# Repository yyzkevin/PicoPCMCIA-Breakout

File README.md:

## Connectors

The PicoPCMCIA External I/O uses Hirose ST-series connectors, chosen for their compact size and robust locking mechanism.

🔗 **Hirose ST Series:**  
https://www.hirose.com/en/product/series/ST

### Connector Part Numbers

| Description | Part Number |
|------------|-------------|
| **Card Receptacle** | ST60-18P(30) |
| **Breakout Plug** | ST60X-18S(30) |
| **Cable Plug Assembly** | ST40X-18S-CV(30) |
| **Cable Bushing** | ST40X-BS(4.0) |
| **Cable Clamp (4 mm)** | ST40X-CM |

## Pinout
| Pin | Signal       | Notes                                                   |
| --: | ------------ | ------------------------------------------------------- |
|   1 | **SWCLK**    | RP2354 Serial Wire Debug (SWD)                          |
|   2 | **SWDIO**    | RP2354 Serial Wire Debug (SWD)                          |
|   3 | **GPIO34**   | User I/O: GPIO, UART0 TX, or I²C1 SDA                   |
|   4 | **GPIO35**   | User I/O: GPIO, UART0 RX, or I²C1 SCL                   |
|   5 | **USB D−**   | RP2354 USB Port                                         |
|   6 | **USB D+**   | RP2354 USB Port                                         |
|   7 | **BOOTSEL**  | Boot select (firmware flashing / recovery)              |
|   8 | **5V**       | 5 V from PC bus (350 mA fused)                          |
|   9 | **GND**      | Ground                                                  |
|  10 | **I2C0 SDA** | I²C master (onboard DSP + external peripherals)         |
|  11 | **I2C0 SCL** | I²C master (onboard DSP + external peripherals)         |
|  12 | —            | Not connected                                           |
|  13 | **GPIO26**   | UART1 TX (also internally connected to SAM2695 MIDI RX) |
|  14 | **IN1_L**    | Line-in left (to DSP)                                   |
|  15 | **IN1_R**    | Line-in right (to DSP)                                  |
|  16 | **HPL**      | Headphones out left (from DSP)                          |
|  17 | **HPR**      | Headphones out right (from DSP)                         |
|  18 | **GND**      | Ground                                                  |

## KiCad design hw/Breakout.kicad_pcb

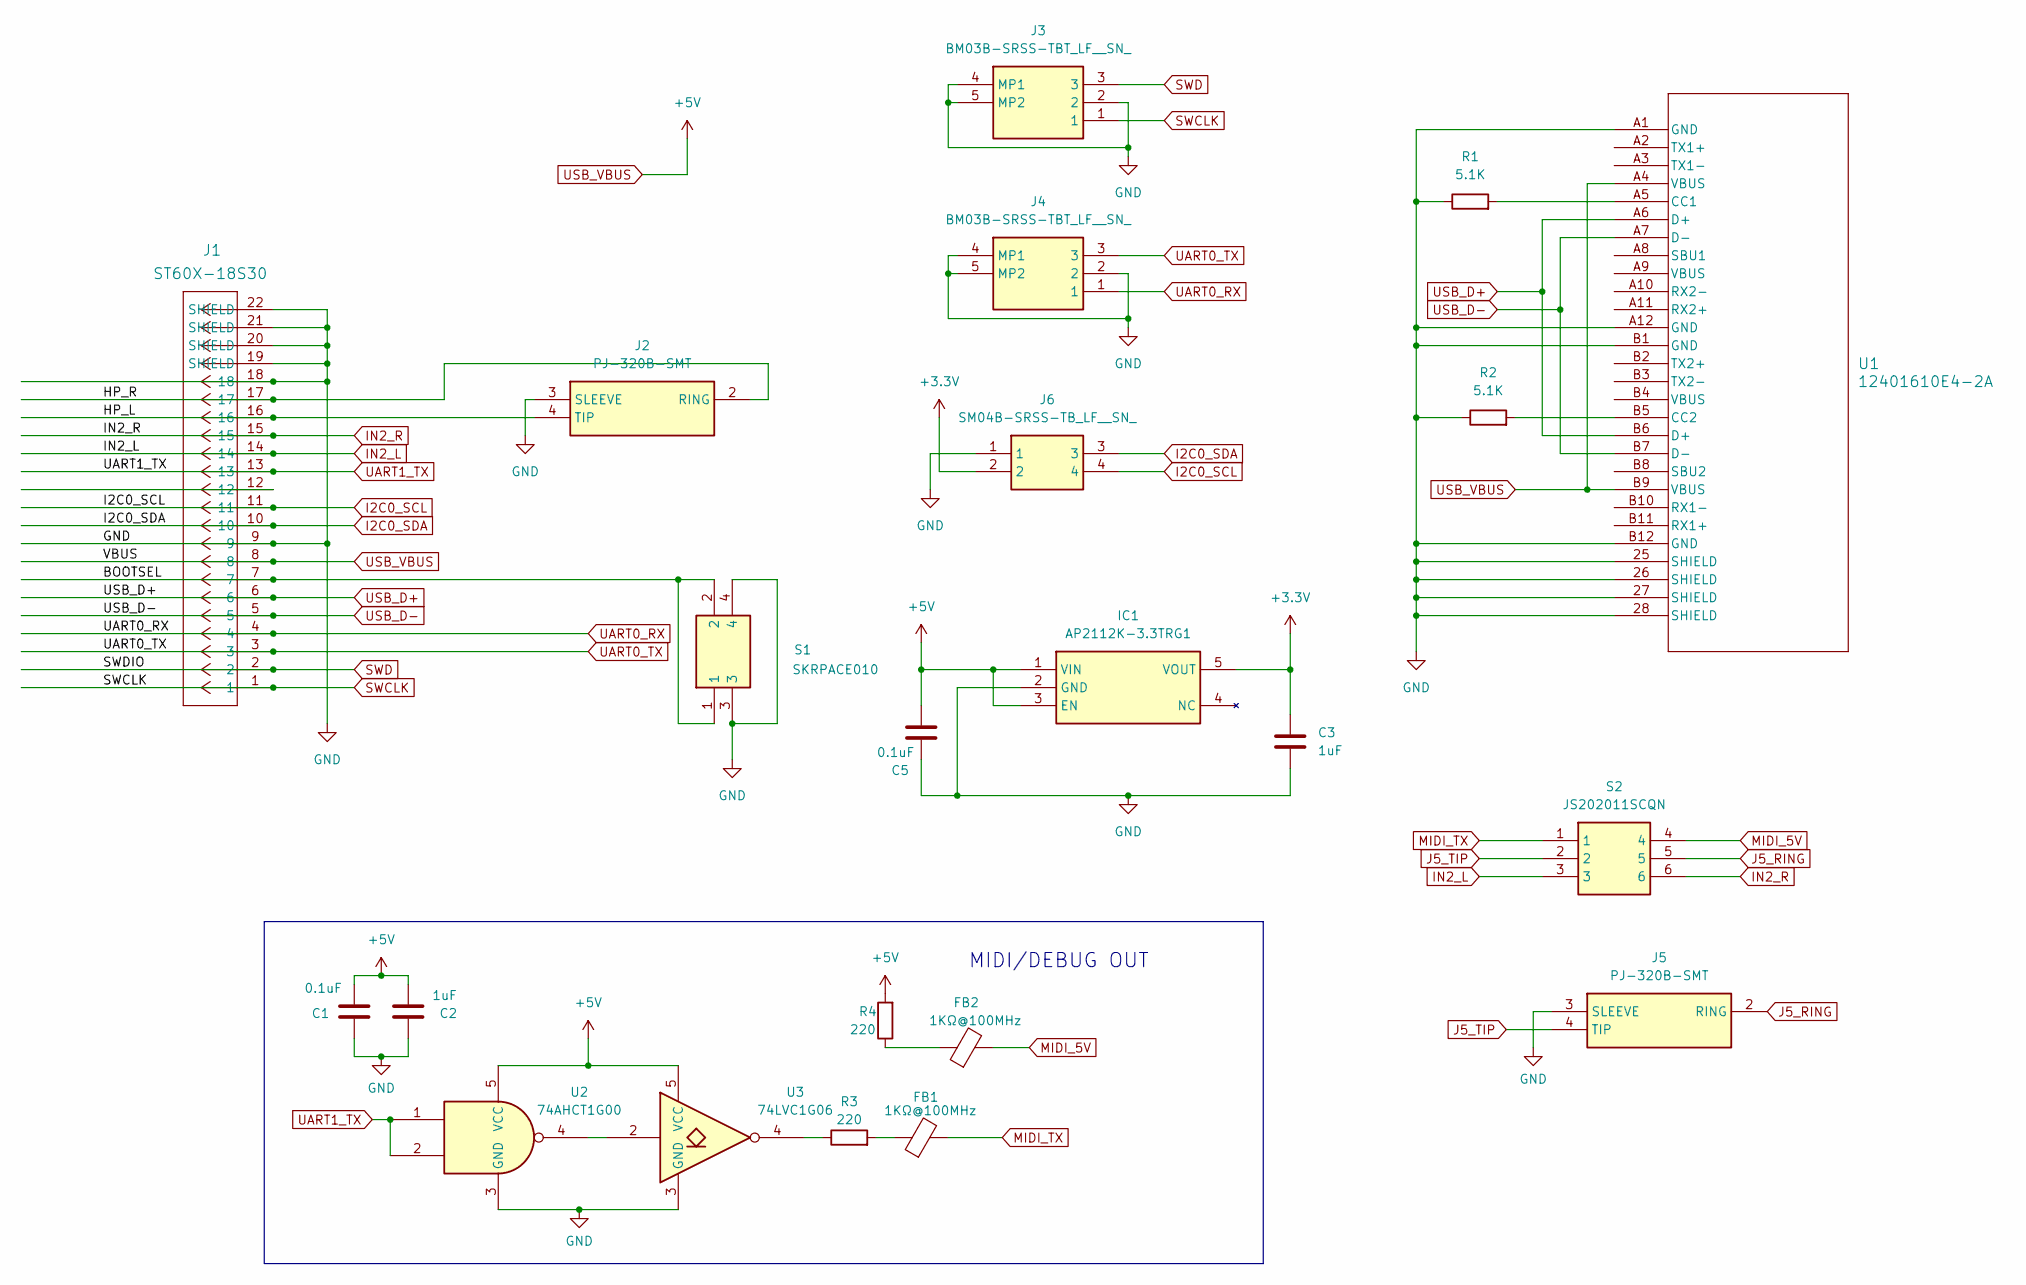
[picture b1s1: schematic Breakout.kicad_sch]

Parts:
C1, C5: 0.1uF; C_0402_1005Metric; LCSC C1525
C2, C3: 1uF; C_0402_1005Metric; LCSC C52923
FB1, FB2: 1KΩ@100MHz; L_0805_2012Metric; LCSC C85835
IC1: AP2112K-3.3TRG1; SOT95P285X140-5N; Mouser Part Number 621-AP2112K-3.3TRG1
J1: ST60X-18S30; CONN18_0X-18S30_HIR; LCSC C21136285
J2, J5: PJ-320B-SMT; Manufacturer_Part_Number PJ-320B-SMT; LCSC C2884998
J3, J4: BM03B-SRSS-TBT_LF__SN_; BM03BSRSSTBTLFSN; Mouser Part Number N/A
J6: SM04B-SRSS-TB_LF__SN_; SM04B-SRSS-TB_LFSN_; Mouser Part Number 306-SM04BSRSSTBLFSN
R1, R2: 5.1K; R_0402_1005Metric; LCSC C25905
R3, R4: 220; R_0402_1005Metric; LCSC C25091
S1: SKRPACE010; SMT_4.2X3.2_; Mouser Part Number 688-SKRPACE010
S2: JS202011SCQN; Mouser Part Number 611-JS202011SCQN
U1: 12401610E4-2A; 12401610E4-2A_AMP; LCSC C5119948
U2: 74AHCT1G00; SOT-353_SC-70-5; LCSC C7483
U3: 74LVC1G06; TSOT-23-5; LCSC C840103

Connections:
+3.3V: C3.1, IC1.5 (VOUT), J6.2
/BOOTSEL: J1.7, S1.1, S1.2
/HP_L: J1.16, J2.4 (TIP)
/HP_R: J1.17, J2.2 (RING)
GND: C1.2, C2.2, C3.2, C5.2, IC1.2 (GND), J1.9, J1.18, J1.19 (SHIELD), J1.20 (SHIELD), J1.21 (SHIELD), J1.22 (SHIELD), J2.3 (SLEEVE), J3.2, J3.4 (MP1), J3.5 (MP2), J4.2, J4.4 (MP1), J4.5 (MP2), J5.3 (SLEEVE), J6.1, R1.1, R2.1, S1.3, S1.4, U1.25 (SHIELD), U1.26 (SHIELD), U1.27 (SHIELD), U1.28 (SHIELD), U1.A1 (GND), U1.A12 (GND), U1.B1 (GND), U1.B12 (GND), U2.3 (GND), U3.3 (GND)
I2C0_SCL: J1.11, J6.4
I2C0_SDA: J1.10, J6.3
IN2_L: J1.14, S2.3
IN2_R: J1.15, S2.6
J5_RING: J5.2 (RING), S2.5
J5_TIP: J5.4 (TIP), S2.2
MIDI_5V: FB2.2, S2.4
MIDI_TX: FB1.2, S2.1
unnamed: FB1.1, R3.2
unnamed: FB2.1, R4.1
unnamed: R3.1, U3.4
unnamed: R1.2, U1.A5 (CC1)
unnamed: R2.2, U1.B5 (CC2)
unnamed: U2.4, U3.2
SWCLK: J1.1, J3.1
SWD: J1.2, J3.3
UART0_RX: J1.4, J4.1
UART0_TX: J1.3, J4.3
UART1_TX: J1.13, U2.1, U2.2
USB_D+: J1.6, U1.A6 (D+), U1.B6 (D+)
USB_D-: J1.5, U1.A7 (D-), U1.B7 (D-)
USB_VBUS: C1.1, C2.1, C5.1, IC1.1 (VIN), IC1.3 (EN), J1.8, R4.2, U1.A4 (VBUS), U1.B9 (VBUS), U2.5 (VCC), U3.5 (VCC)

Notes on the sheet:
MIDI/DEBUG OUT

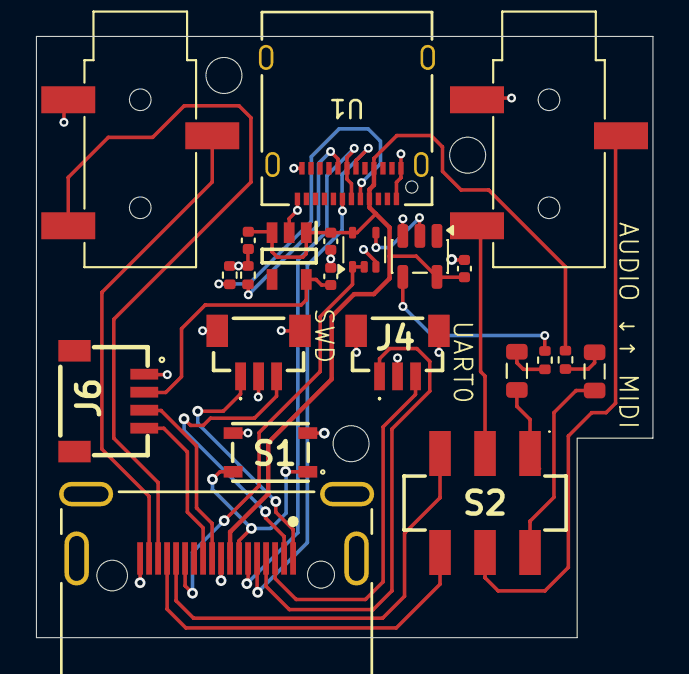
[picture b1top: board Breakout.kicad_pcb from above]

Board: 2 copper layers, 34.2 x 33.4 mm, 22 parts (0 on the bottom side), 27 nets.

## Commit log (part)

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2026-01-06 Initial Commit
    Work in progress breakout board
2026-01-06 Add connector details and pinout to README
    Added detailed information about connectors and pinout for PicoPCMCIA External I/O.
2026-01-09 Work in progress
